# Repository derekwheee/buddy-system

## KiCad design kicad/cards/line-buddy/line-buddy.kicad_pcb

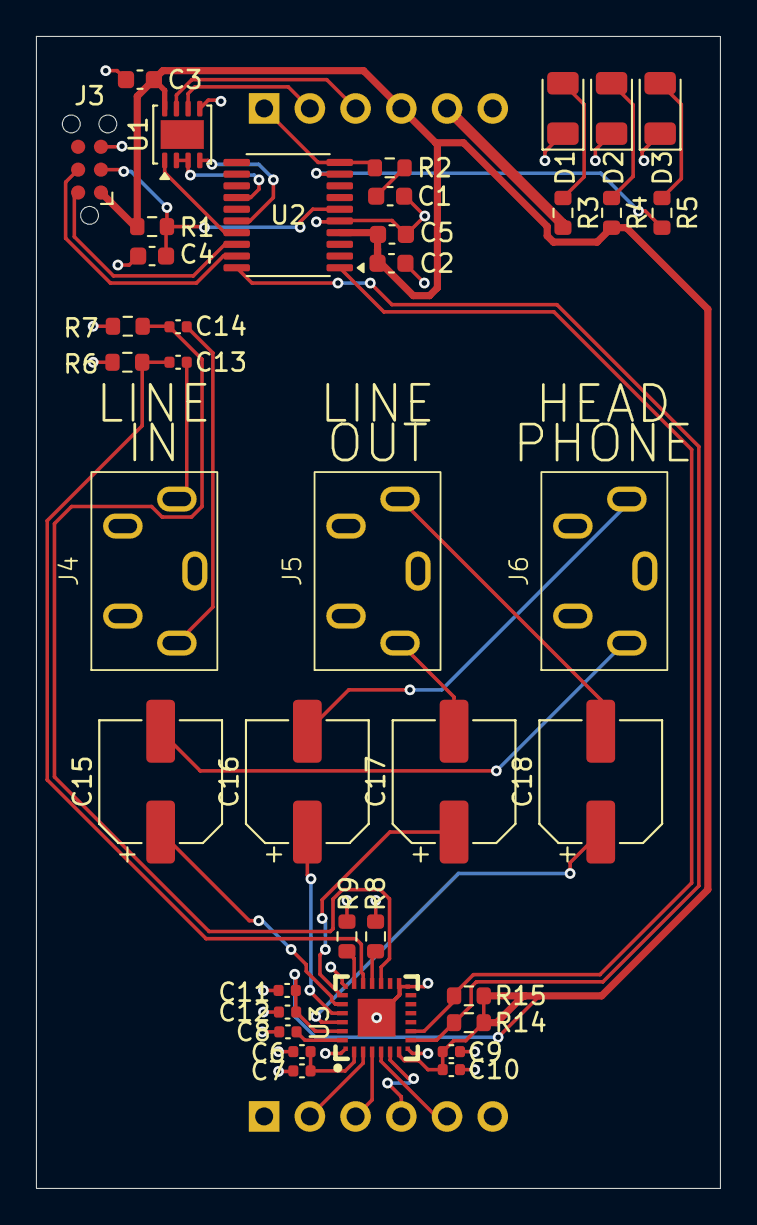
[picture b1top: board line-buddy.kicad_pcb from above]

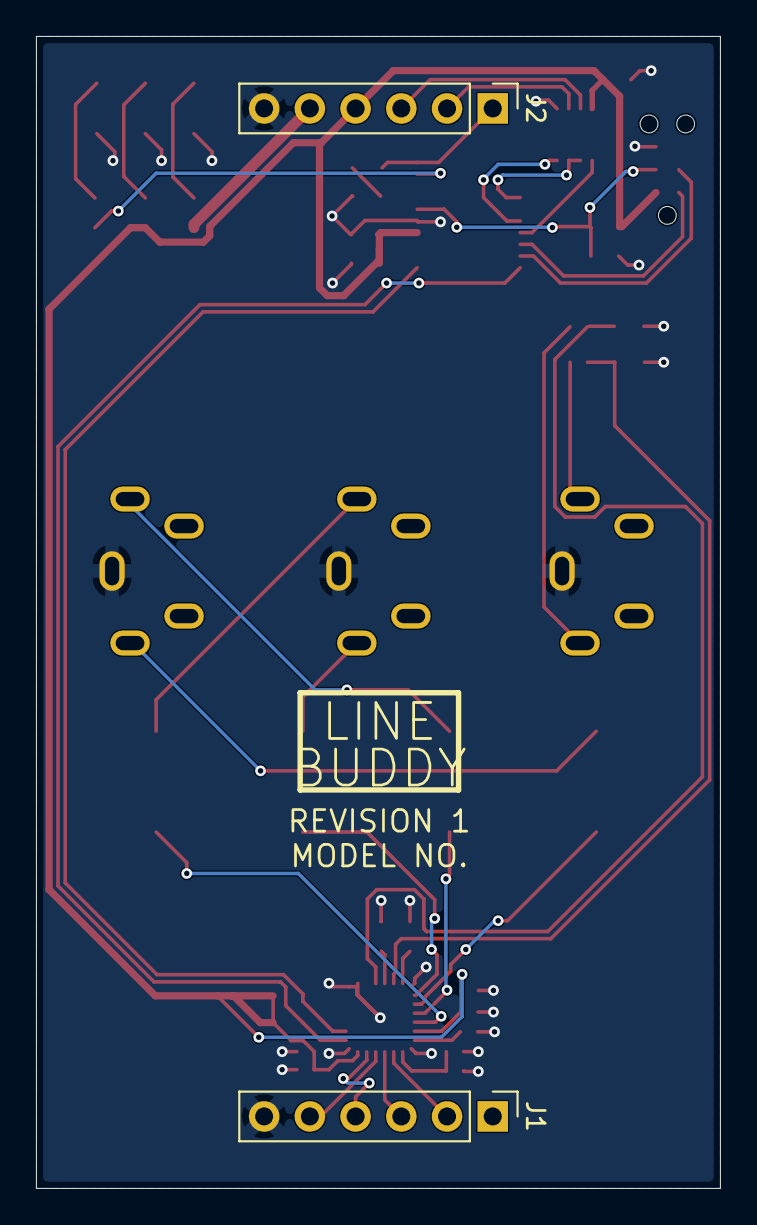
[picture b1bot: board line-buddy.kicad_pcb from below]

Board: 2 copper layers, 38.0 x 64.0 mm, 41 parts (2 on the bottom side), 39 nets.

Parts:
C1, C2, C3, C4: 100n; C_0603_1608Metric
C5: 1u; C_0603_1608Metric
C6, C9, C11: 0.1u; C_0402_1005Metric
C7, C10, C12, C13, C14: 10u; C_0402_1005Metric
C8: 1u; C_0402_1005Metric
C15, C16, C17, C18: 47u; CP_Elec_6.3x5.4
D1, D2, D3: LED; LED_1206_3216Metric
J1, J2: Conn_01x06_Pin; PinHeader_1x06_P2.54mm_Vertical
J3: Conn_ARM_SWD_TagConnect_TC2030-NL; Tag-Connect_TC2030-IDC-NL_2x03_P1.27mm_Vertical
J4: AnalogIn; PJ-358
J5: LineOut; PJ-358
J6: HeadphoneOut; PJ-358
R1: 10K; R_0603_1608Metric
R2, R3, R4, R5: 1K; R_0603_1608Metric
R6, R7, R8, R9: 100K; R_0603_1608Metric
R14, R15: 4.7K; R_0603_1608Metric
U1: THVD1450DR; VSON-8-1EP_3x3mm_P0.65mm_EP1.6x2.4mm
U2: STM32C011F4Px; TSSOP-20_4.4x6.5mm_P0.65mm
U3: TAC5112; VQFN-24_L4.0-W4.0-P0.50-BL-EP2.1_1

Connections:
+5V: J2.5, R3.2
AVDD: C2.1, C3.1, C5.1, C9.2, C10.2, C11.2, C12.2, J2.4, J3.1 (VCC), R1.2, R4.2, R14.2, R15.2, U1.8 (VCC), U2.4 (VDD), U3.6 (IOVDD), U3.23 (AVDD)
BLCK: J1.2, U3.2 (BCLK)
BUS A: J2.2, U1.6 (A)
BUS B: J2.3, U1.7 (B)
BUS_EN: U1.2 (~RE), U1.3 (DE), U2.14 (PA7)
BUS_RX: U1.1 (RO), U2.17 (PA10/PA12)
BUS_TX: U1.4 (DI), U2.16 (PA9/PA11)
DREG: C6.2, C7.2, U3.1 (DREG)
FSYNC: J1.3, U3.3 (FSYNC)
GND: C1.2, C2.2, C3.2, C4.2, C5.2, C6.1, C7.1, C8.1, C9.1, C10.1, C11.1, C12.1, D1.1 (K), D2.1 (K), D3.1 (K), J1.6, J2.6, J3.5 (GND), J4.S, J5.S, J6.S, R6.2, R7.2, R8.2, R9.2, U1.5 (GND), U2.5 (VSS), U3.13 (ADDR), U3.25 (VSS), U3.A1 (VSS), U3.A2 (VSS), U3.A3 (VSS), U3.A4 (VSS)
HP_OUT_L: C15.2, J6.T
HP_OUT_R: C16.2, J6.R
IN1M: R8.1, U3.16 (IN1M)
IN1P: C14.2, R7.1, U3.15 (IN1P)
IN2M: R9.1, U3.18 (IN2M)
IN2P: C13.2, R6.1, U3.17 (IN2P)
LINE_OUT_L: C17.2, J5.T
LINE_OUT_R: C18.2, J5.R
MISO: J1.5, U3.4 (DOUT)
MOSI: J1.4, U3.5 (DIN)
NRST: C4.1, J3.3 (~RESET), R1.1, U2.6 (PF2)
unnamed: C1.1, R2.1
unnamed: C13.1, J4.R
unnamed: C14.1, J4.T
unnamed: D1.2 (A), R3.1
unnamed: D2.2 (A), R4.1
unnamed: D3.2 (A), R5.1
OUT1M: C17.1, U3.19 (OUT1M)
OUT1P: C15.1, U3.20 (OUT1P)
OUT2M: C18.1, U3.22 (OUT2M)
OUT2P: C16.1, U3.21 (OUT2P)
PA2: R5.2, U2.9 (PA2)
SCL: R14.1, U2.20 (PB6), U3.7 (SCL)
SDA: R15.1, U2.1 (PB7), U3.8 (SDA)
SLOT: J2.1, R2.2, U2.10 (PA3)
SWCLK: J3.4 (SWCLK), U2.19 (PA14)
SWDIO: J3.2 (SWDIO), U2.18 (PA13)
VREF: C8.2, U3.24 (VREF)

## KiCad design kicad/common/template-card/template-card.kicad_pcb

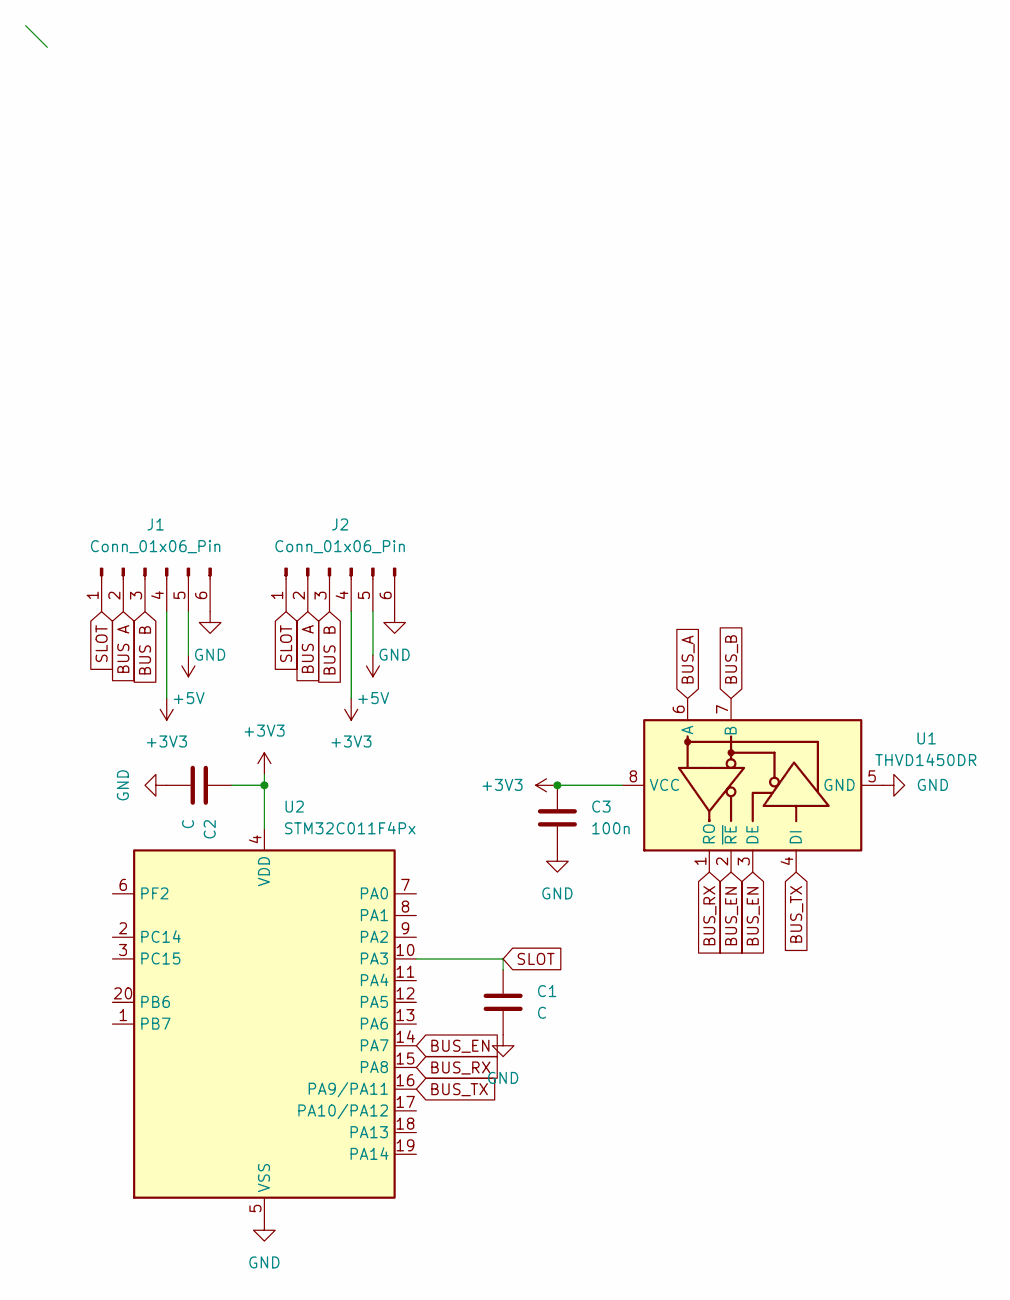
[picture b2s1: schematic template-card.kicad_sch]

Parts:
C1, C2: C; C_0603_1608Metric
C3: 100n; C_0603_1608Metric
J1, J2: Conn_01x06_Pin; PinHeader_1x06_P2.54mm_Vertical
U1: THVD1450DR; VSON-8-1EP_3x3mm_P0.65mm_EP1.6x2.4mm
U2: STM32C011F4Px; TSSOP-20_4.4x6.5mm_P0.65mm

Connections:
+3V3: C2.1, C3.1, J1.4, J2.4, U1.8 (VCC), U2.4 (VDD)
+5V: J1.5, J2.5
BUS A: J1.2, J2.2
BUS B: J1.3, J2.3
BUS_A: U1.6 (A)
BUS_B: U1.7 (B)
BUS_EN: U1.2 (~RE), U1.3 (DE), U2.14 (PA7)
BUS_RX: U1.1 (RO), U2.15 (PA8)
BUS_TX: U1.4 (DI), U2.16 (PA9/PA11)
GND: C1.2, C2.2, C3.2, J1.6, J2.6, U1.5 (GND), U2.5 (VSS)
SLOT: C1.1, J1.1, J2.1, U2.10 (PA3)

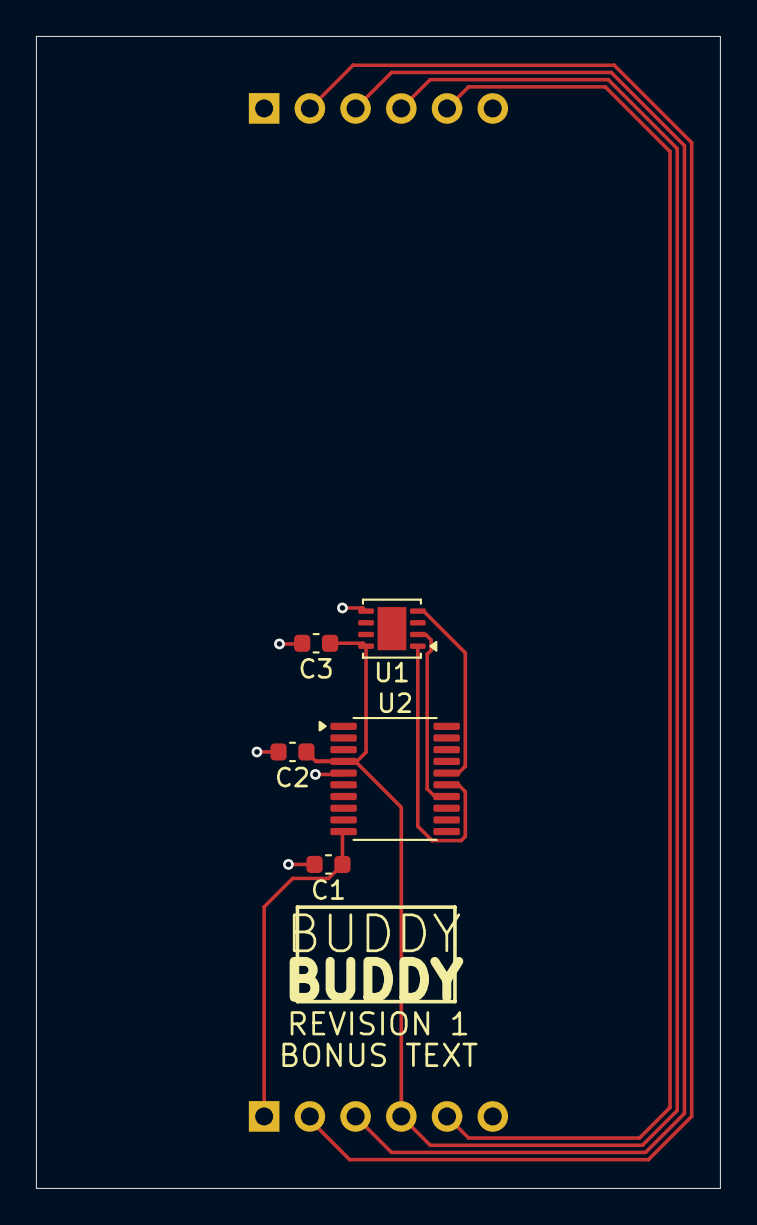
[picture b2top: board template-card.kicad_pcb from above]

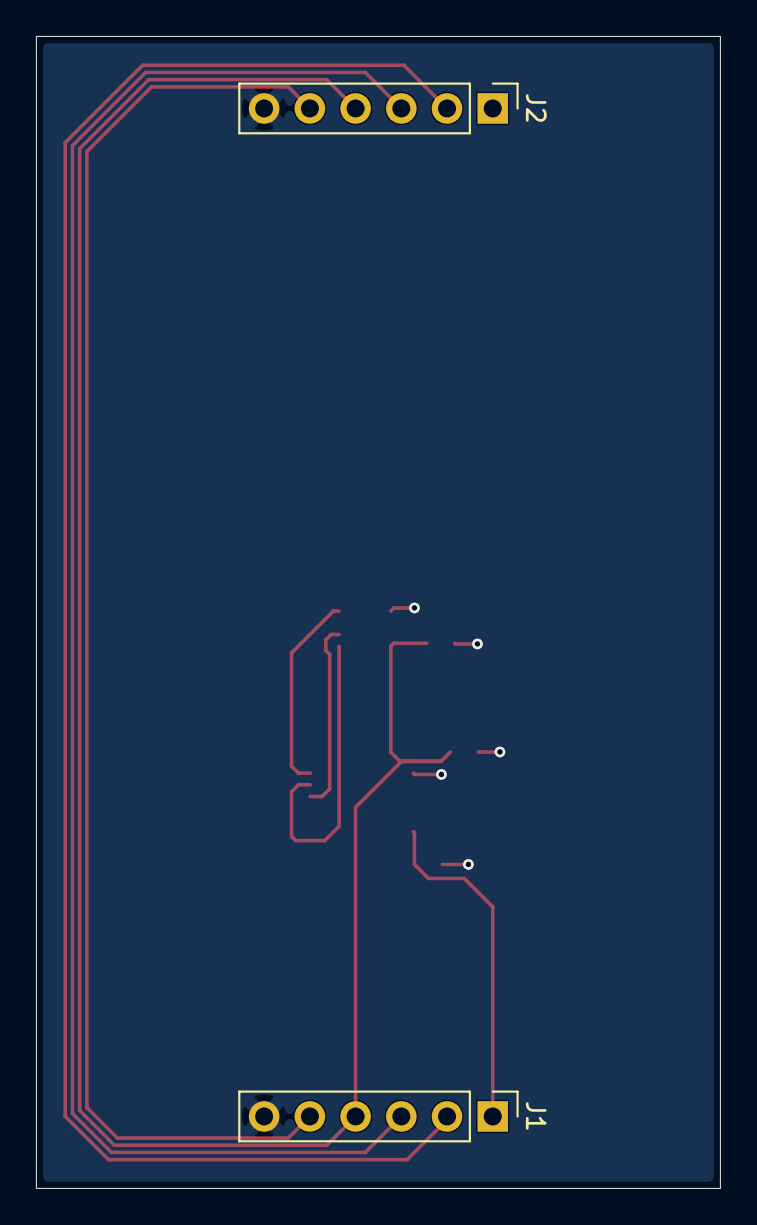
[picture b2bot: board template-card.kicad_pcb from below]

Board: 2 copper layers, 38.0 x 64.0 mm, 7 parts (2 on the bottom side), 9 nets.

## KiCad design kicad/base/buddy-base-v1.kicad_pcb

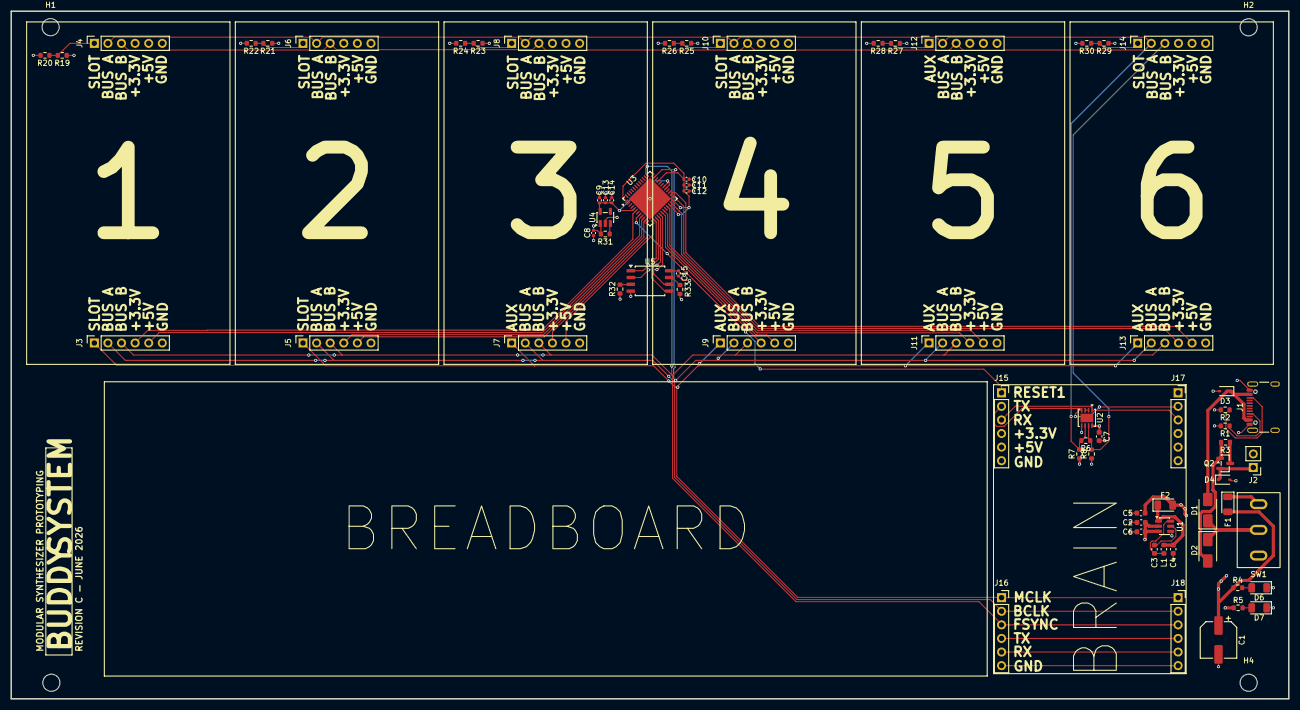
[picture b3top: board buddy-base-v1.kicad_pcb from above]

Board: 4 copper layers, 238.8 x 128.5 mm, 76 parts (0 on the bottom side), 53 nets.

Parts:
C1: 100u; CP_Elec_6.3x7.7
C2: 10u; C_0603_1608Metric
C3, C5, C6, C7: 100n; C_0603_1608Metric
C4: 44u; C_0603_1608Metric
C8, C9, C12: 1u; C_0402_1005Metric
C10, C13: 10n; C_0402_1005Metric
C11, C14, C15: 100n; C_0402_1005Metric
D1, D2: D_Schottky; D_SMA
D3, D4: D_TVS; D_SOD-323
D6, D7: LED; LED_1206_3216Metric
F1: 2A; D_1206_3216Metric
F2: 1A; D_1206_3216Metric
H1, H2, H3, H4: MountingHole; MountingHole_3.2mm_M3
J1: USB_C_Receptacle; USB_C_Receptacle_GCT_USB4105-xx-A_16P_TopMnt_Horizontal
J2: Conn_01x02_Socket; PinHeader_1x02_P2.54mm_Vertical
J3, J4, J5, J6, J7, J8, J9, J10, J11, J12, J13, J14: Conn_01x06_Socket; PinSocket_1x06_P2.54mm_Vertical
J15, J16, J17, J18: Conn_01x06; PinSocket_1x06_P2.54mm_Vertical
L1: 4.7u; L_0603_1608Metric
Q2: AO3401A; SOT-23
R1, R2: 5K1; R_0603_1608Metric
R3, R20, R22, R24, R25, R26, R28, R30: 100K; R_0603_1608Metric
R4, R5: 1K; R_0603_1608Metric
R6: 120; R_0603_1608Metric
R7, R8: 680; R_0603_1608Metric
R19: 10K; R_0603_1608Metric
R21: 22K; R_0603_1608Metric
R23: 47K; R_0603_1608Metric
R27: 220K; R_0603_1608Metric
R29: 470K; R_0603_1608Metric
R31, R32, R33: R; R_0603_1608Metric
SW1: SW_SPDT; SS12D10G5
U1: AP63203WU; TSOT-23-6
U2: THVD1450DR; VSON-8-1EP_3x3mm_P0.65mm_EP1.6x2.4mm
U3: ICE40UP5K-SG48ITR; QFN-48-1EP_7x7mm_P0.5mm_EP5.6x5.6mm
U4: AP2127K-1.2; SOT-23-5
U5: W25Q32JVSS; SOIC-8_5.3x5.3mm_P1.27mm

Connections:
3V3_SYS: C5.1, C7.1, C8.2, C10.1, C11.1, C12.1, C15.1, F2.2, J4.4, J6.4, J8.4, J10.4, J12.4, J14.4, J15.4, J17.4, R5.1, R7.1, R19.1, R21.1, R23.1, R25.1, R27.1, R29.1, R31.2, R32.1, R33.1, U2.8 (VCC), U3.1 (VCCIO_2), U3.22 (SPI_VCCIO1), U3.24 (VPP_2V5), U3.33 (VCCIO_0), U4.1 (VIN), U5.8 (VCC)
5V_SYS: C1.1, C2.1, C6.1, F1.2, J4.5, J6.5, J8.5, J10.5, J12.5, J14.5, J15.5, J17.5, R4.1, U1.2 (EN), U1.3 (IN)
BLCK: J3.2, J5.2, J7.2, J9.2, J11.2, J13.2, J16.2, J18.2, U3.35 (IOT_46b_G0)
BUS_A: J4.2, J6.2, J8.2, J10.2, J12.2, J14.2, R6.2, R7.2, U2.6 (A)
BUS_B: J4.3, J6.3, J8.3, J10.3, J12.3, J14.3, R6.1, R8.2, U2.7 (B)
BUS_EN: U2.2 (~RE), U2.3 (DE)
BUS_RX: J15.3, J17.3, U2.1 (RO)
BUS_TX: J15.2, J17.2, U2.4 (DI)
FPGA_1V2: C9.2, C13.1, C14.1, U3.5 (VCC), U3.29 (VCCPLL), U3.30 (VCC), U4.5 (VOUT)
FPGA_SPI_SCK: U3.15 (IOB_34a_SPI_SCK), U5.6 (CLK)
FPGA_SPI_SI: U3.17 (IOB_33b_SPI_SI), U5.2 (DO/IO_{1})
FPGA_SPI_SO: U3.14 (IOB_32a_SPI_SO), U5.5 (DI/IO_{0})
FPGA_SPI_SS: U3.16 (IOB_35b_SPI_SS), U5.1 (~CS)
FSYNC: J3.3, J5.3, J7.3, J9.3, J11.3, J13.3, J16.3, J18.3, U3.37 (IOT_45a_G1)
GND: C1.2, C2.2, C4.2, C5.2, C6.2, C7.2, C8.1, C9.1, C10.2, C11.2, C12.2, C13.2, C14.2, C15.2, D3.2 (A2), D4.2 (A2), D6.1 (K), D7.1 (K), J1.A1 (GND), J1.A12 (GND), J1.B1 (GND), J1.B12 (GND), J1.SH (SHIELD), J2.2, J3.6, J4.6, J5.6, J6.6, J7.6, J8.6, J9.6, J10.6, J11.6, J12.6, J13.6, J14.6, J15.6, J16.6, J17.6, J18.6, R1.2, R2.2, R8.1, R20.2, R22.2, R24.2, R26.2, R28.2, R30.2, U1.4 (GND), U2.5 (GND), U3.49 (GND), U4.2 (GND), U5.4 (GND)
MCLK: J3.1, J5.1, J7.1, J9.1, J11.1, J13.1, J16.1, J18.1
unnamed: D1.2 (A), D3.1 (A1), J1.A4 (VBUS), J1.A9 (VBUS), J1.B4 (VBUS), J1.B9 (VBUS)
unnamed: D2.2 (A), Q2.1 (G), R3.2
unnamed: D4.1 (A1), J2.1, Q2.2 (S)
unnamed: D6.2 (A), R4.2
unnamed: D7.2 (A), R5.2
unnamed: J1.A5 (CC1), R1.1
unnamed: J1.B5 (CC2), R2.1
unnamed: Q2.3 (D), R3.1
unnamed: F1.1, SW1.1 (A)
unnamed: C3.2, L1.1, U1.6 (BST)
unnamed: C4.1, F2.1, L1.2, U1.1 (FB)
unnamed: C3.1, U1.5 (SW)
unnamed: R31.1, U4.3 (EN)
unnamed: R33.2, U5.7 (~HOLD/~RESET/IO_{3})
unnamed: R32.2, U5.3 (~WP/IO_{2})
RESET_1: J15.1, U3.8 (~CRESET)
S1_AUDIO_IN: J3.4, U3.6 (IOB_13b)
S1_AUDIO_OUT: J3.5, U3.9 (IOB_16a)
S2_AUDIO_IN: J5.4, U3.10 (IOB_18a)
S2_AUDIO_OUT: J5.5, U3.11 (IOB_20a)
S3_AUDIO_IN: J7.4, U3.12 (IOB_22a)
S3_AUDIO_OUT: J7.5, U3.13 (IOB_24a)
S4_AUDIO_IN: J9.4, U3.18 (IOB_31b)
S4_AUDIO_OUT: J9.5, U3.19 (IOB_29b)
S5_AUDIO_IN: J11.4, U3.21 (IOB_23b)
S5_AUDIO_OUT: J11.5, U3.23 (IOT_37a)
S6_AUDIO_IN: J13.4, U3.25 (IOT_36b)
S6_AUDIO_OUT: J13.5, U3.26 (IOT_39a)
SLOT_1: J4.1, R19.2, R20.1
SLOT_2: J6.1, R21.2, R22.1
SLOT_3: J8.1, R23.2, R24.1
SLOT_4: J10.1, R25.2, R26.1
SLOT_5: J12.1, R27.2, R28.1
SLOT_6: J14.1, R29.2, R30.1
TDM_RX: J16.5, J18.5
TDM_TX: J16.4, J18.4
VIN_OR: D1.1 (K), D2.1 (K), SW1.2 (B)

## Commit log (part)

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2026-06-13 Add Card template
2026-06-14 Remove J3 from BOM
2026-06-14 Scaffold web
2026-06-15 Remove author card
2026-06-15 Update homepage content
2026-06-23 Add Buddy Audio bus
2026-06-28 Update cards
2026-06-29 Add new line buddy WIP
2026-06-29 Finish Line Buddy
